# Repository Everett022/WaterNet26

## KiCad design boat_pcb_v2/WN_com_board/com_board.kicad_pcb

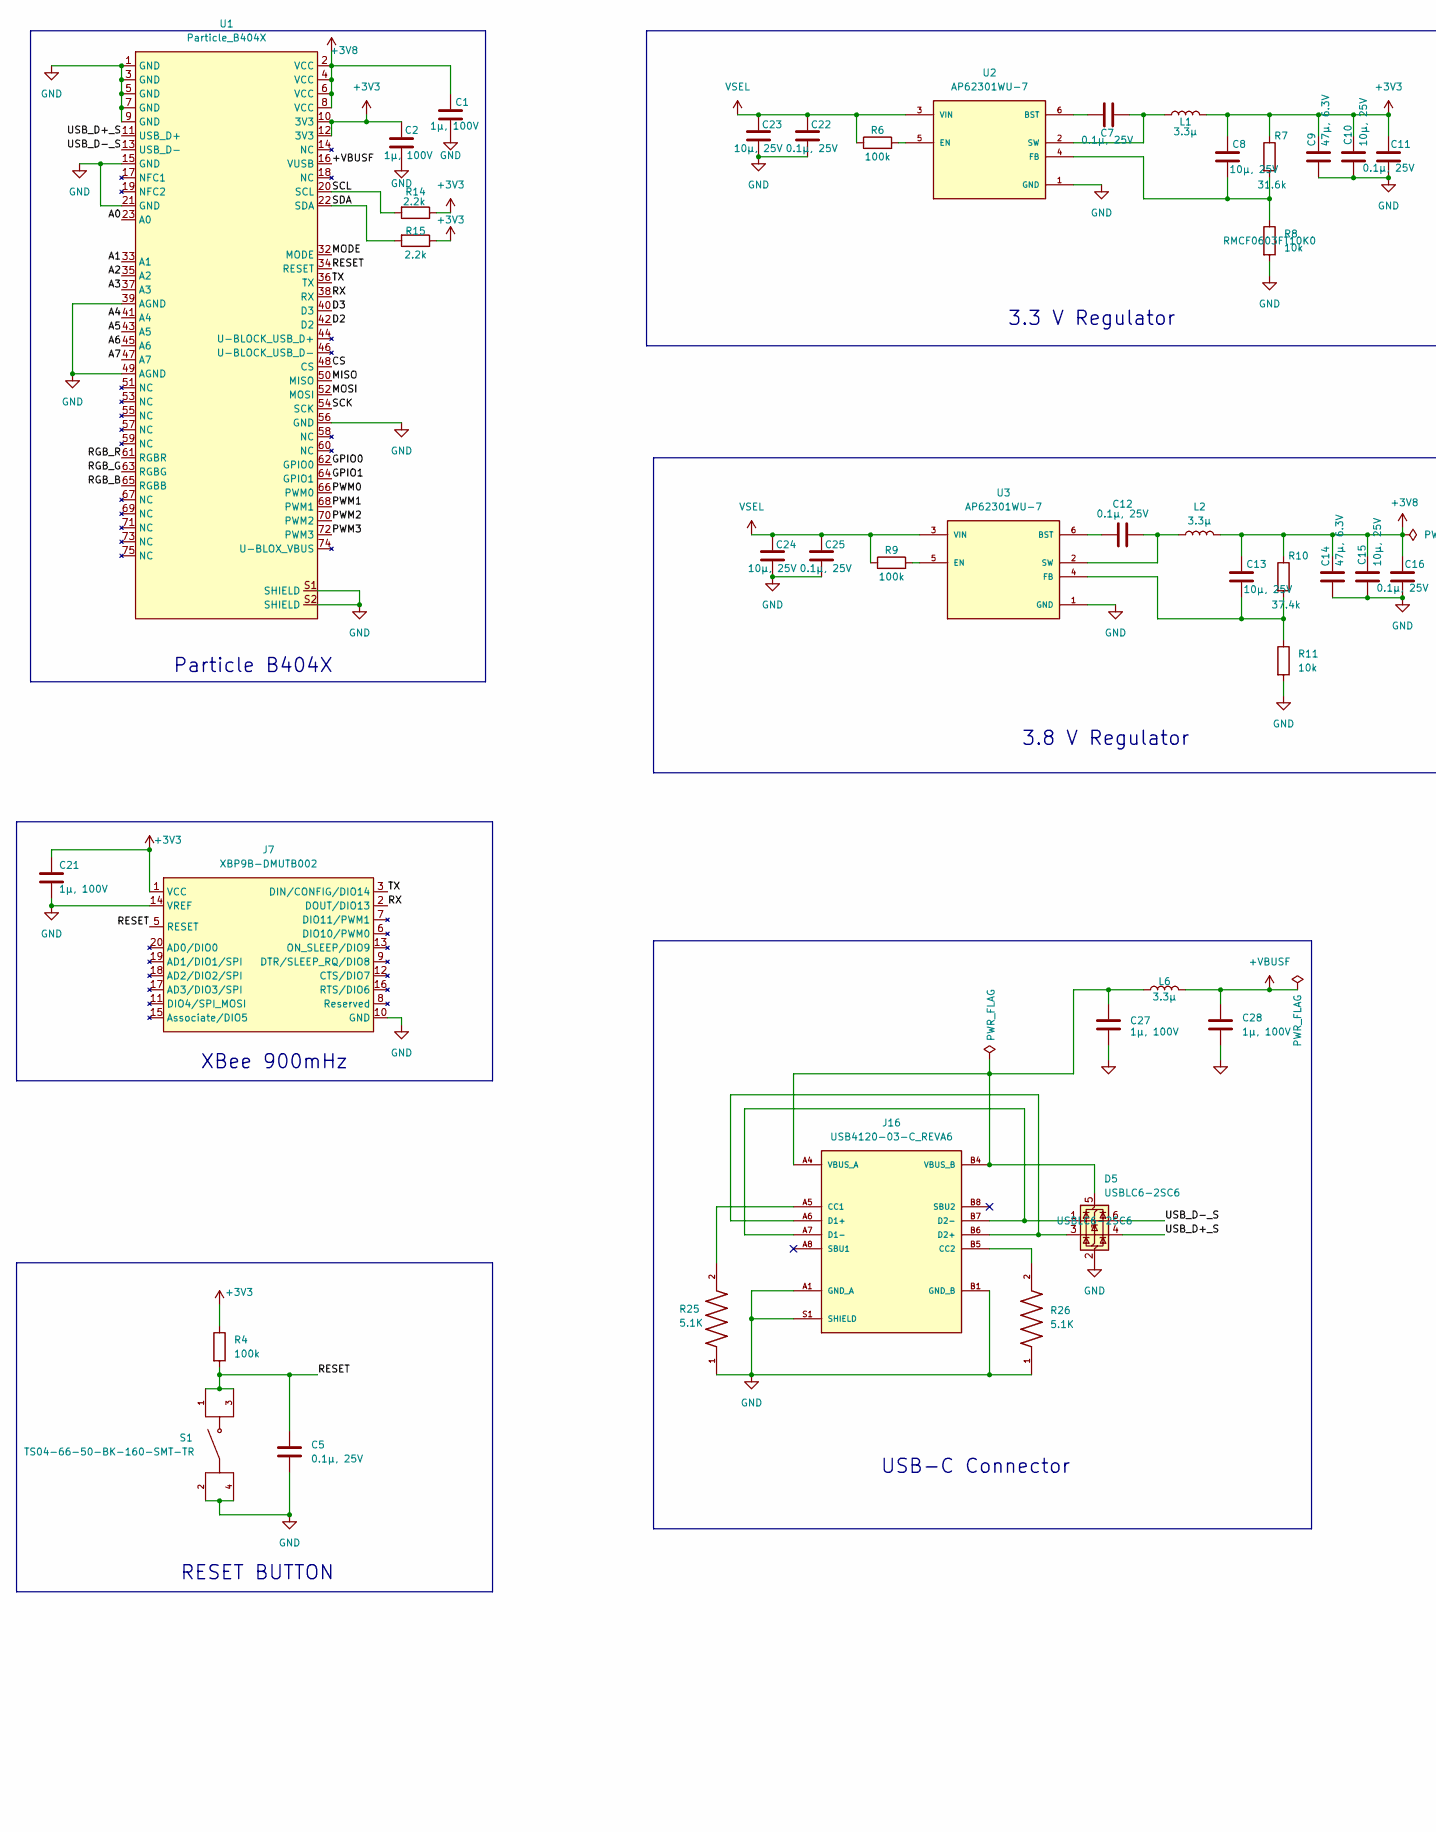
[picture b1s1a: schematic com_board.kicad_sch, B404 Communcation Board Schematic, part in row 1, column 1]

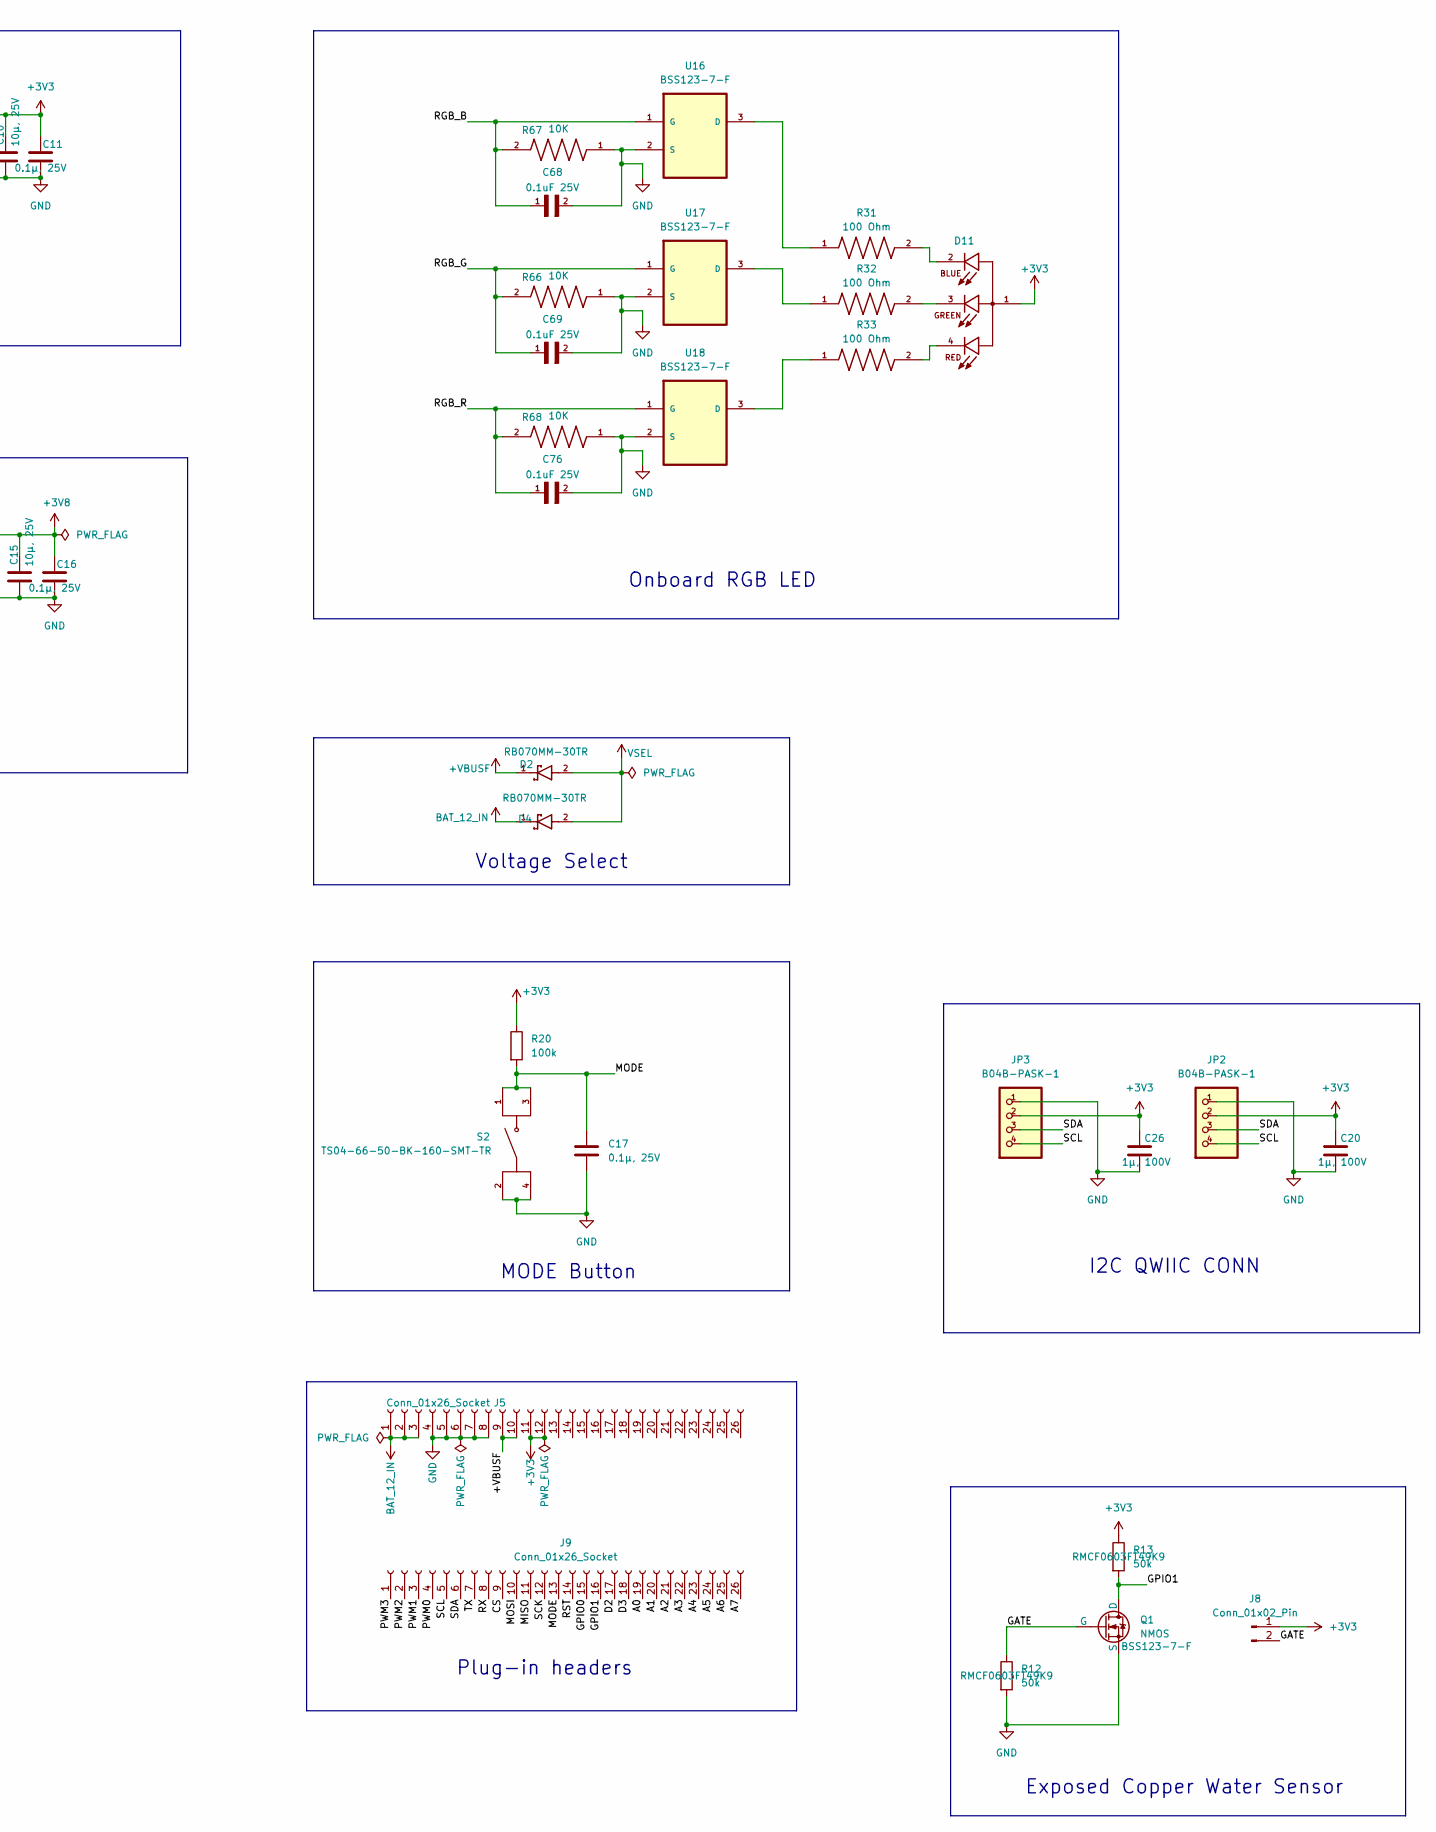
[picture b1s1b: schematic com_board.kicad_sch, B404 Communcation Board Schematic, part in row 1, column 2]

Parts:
C1, C2, C20, C21, C26, C27, C28: 1µ, 100V; CAPC2012X145N
C5, C7, C11, C12, C16, C17, C22, C25: 0.1µ, 25V; CAPC2012X95N
C8, C10, C13, C15, C23, C24: 10µ, 25V; CAPC2012X145N
C9, C14: 47µ, 6.3V; CAPC3216X180N
C68, C69, C76: 0.1uF 25V; CAPC2012X95N
D2, D4: RB070MM-30TR; DIO_RB070MM-30TR
D5: USBLC6-2SC6; SOT-23-6
D11: CLMVC-FKA-CL1D1L71BB7C3C3; LED_CLMVC-FKA-CL1D1L71BB7C3C3; PARTREV 14
J5, J9: Conn_01x26_Socket; PinHeader_1x26_P2.54mm_Vertical
J7: XBP9B-DMUTB002; SULLINS_NPPN101BFCN-RC
J8: Conn_01x02_Pin; PinHeader_1x02_P2.54mm_Vertical
J16: USB4120-03-C_REVA6; GCT_USB4120-03-C_REVA6; PARTREV A6
JP2, JP3: B04B-PASK-1
L1, L2, L6: 3.3µ; INDC1608X95N
Q1: NMOS; SOT95P240X110-3N
R4, R6, R9, R20: 100k; RES_ERA6AEB104V
R7: 31.6k; RES_ERA6AEB3162V
R8, R11: 10k; RES_ERA6AEB103V
R10: 37.4k; RESC1608X55N
R12, R13: 50k; RESC1608X55N
R14, R15: 2.2k; RESC1608X55N
R25, R26: 5.1K; RESC1508X55N
R31, R32, R33: 100 Ohm; RES_ERJ3EKF1000V; PARTREV 3/1/2020
R66, R67, R68: 10K; RES_ERA6AEB103V; PARTREV 3/1/2020
S1, S2: TS04-66-50-BK-160-SMT-TR; SW_TS04-66-50-BK-160-SMT-TR; PARTREV 1.04mm
U1: Particle_B404X; b404x
U2, U3: AP62301WU-7; SOT95P280X100-6N; PARTREV Rev. 3 - 2
U16, U17, U18: BSS123-7-F; SOT95P240X110-3N; MPN BSS123-7-F

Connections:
+3V3: C2.1, C8.1, C9.1, C10.1, C11.1, C20.1, C21.1, C26.1, D11.1, J5.11, J5.12, J7.1 (VCC), J8.1, JP2.2, JP3.2, L1.2, R4.1, R7.1, R13.1, R14.1, R15.1, R20.1, U1.10 (3V3), U1.12 (3V3); also elsewhere on the board
+3V8: C1.1, C13.1, C14.1, C15.1, C16.1, L2.2, R10.1, U1.2 (VCC), U1.4 (VCC), U1.6 (VCC), U1.8 (VCC)
+VBUSF: C28.1, D2.1, J5.9, J5.10, L6.2, U1.16 (VUSB); also elsewhere on the board
/A0: J9.19, U1.23 (A0)
/A1: J9.20, U1.33 (A1)
/A2: J9.21, U1.35 (A2)
/A3: J9.22, U1.37 (A3)
/A4: J9.23, U1.41 (A4)
/A5: J9.24, U1.43 (A5)
/A6: J9.25, U1.45 (A6)
/A7: J9.26, U1.47 (A7)
/CS: J9.9, U1.48 (CS)
/D2: J9.17, U1.42 (D2)
/D3: J9.18, U1.40 (D3)
/GATE: J8.2, Q1.2 (G), R12.1
/GPIO0: J9.15, U1.62 (GPIO0)
/GPIO1: J9.16, Q1.1 (D), R13.2, U1.64 (GPIO1)
/MISO: J9.11, U1.50 (MISO)
/MODE: C17.1, J9.13, R20.2, S2.1, S2.3, U1.32 (MODE)
/MOSI: J9.10, U1.52 (MOSI)
/PWM0: J9.4, U1.66 (PWM0)
/PWM1: J9.3, U1.68 (PWM1)
/PWM2: J9.2, U1.70 (PWM2)
/PWM3: J9.1, U1.72 (PWM3)
/RESET: C5.1, J7.5 (RESET), R4.2, S1.1, S1.3, U1.34 (RESET)
/RGB_B: C68.1, R67.2, U1.65 (RGBB), U16.1 (G)
/RGB_G: C69.1, R66.2, U1.63 (RGBG), U17.1 (G)
/RGB_R: C76.1, R68.2, U1.61 (RGBR), U18.1 (G)
/RST: J9.14
/RX: J7.2 (DOUT/DIO13), J9.8, U1.38 (RX)
/SCK: J9.12, U1.54 (SCK)
/SCL: J9.5, JP2.4, JP3.4, R14.2, U1.20 (SCL)
/SDA: J9.6, JP2.3, JP3.3, R15.2, U1.22 (SDA)
/TX: J7.3 (DIN/CONFIG/DIO14), J9.7, U1.36 (TX)
/USB_D+_S: D5.4 (I/O2), U1.11 (USB_D+); also elsewhere on the board
/USB_D-_S: D5.6 (I/O1), U1.13 (USB_D-); also elsewhere on the board
BAT_12_IN: D4.1, J5.1, J5.2, J5.3
GND: C1.2, C2.2, C5.2, C9.2, C10.2, C11.2, C14.2, C15.2, C16.2, C17.2, C20.2, C21.2, C22.2, C23.2, C24.2, C25.2, C26.2, C27.2, C28.2, C68.2, C69.2, C76.2, D5.2 (GND), J5.4, J5.5, J5.6, J5.7, J5.8, J7.10 (GND), J7.14 (VREF), J16.A1 (GND_A), J16.A12 (GND_A), J16.B1 (GND_B), J16.B12 (GND_B), J16.S1 (SHIELD), J16.S2 (SHIELD), J16.S3 (SHIELD), J16.S4 (SHIELD), JP2.1, JP3.1, Q1.3 (S), R8.2, R11.2, R12.2, R25.1, R26.1, R66.1, R67.1, R68.1, S1.2, S1.4, S2.2, S2.4, U1.1 (GND), U1.3 (GND), U1.5 (GND), U1.7 (GND), U1.9 (GND), U1.15 (GND), U1.21 (GND), U1.39 (AGND), U1.49 (AGND), U1.56 (GND), U1.S1 (SHIELD), U1.S2 (SHIELD), U2.1 (GND), U3.1 (GND), U16.2 (S), U17.2 (S), U18.2 (S); also elsewhere on the board
unnamed: D11.2, R31.2
unnamed: D11.3, R32.2
unnamed: D11.4, R33.2
unnamed: J16.A5 (CC1), R25.2
unnamed: J16.B5 (CC2), R26.2
unnamed: D5.3 (I/O2), J16.A6 (D1+), J16.B6 (D2+)
unnamed: D5.1 (I/O1), J16.A7 (D1-), J16.B7 (D2-)
unnamed: C7.1, U2.6 (BST)
unnamed: R6.2, U2.5 (EN)
unnamed: C8.2, R7.2, R8.1, U2.4 (FB)
unnamed: C7.2, L1.1, U2.2 (SW)
unnamed: C12.1, U3.6 (BST)
unnamed: R9.2, U3.5 (EN)
unnamed: C13.2, R10.2, R11.1, U3.4 (FB)
unnamed: C12.2, L2.1, U3.2 (SW)
unnamed: R31.1, U16.3 (D)
unnamed: R32.1, U17.3 (D)
unnamed: R33.1, U18.3 (D)
VBUS_A: C27.1, D5.5 (VBUS), J16.A4 (VBUS_A), J16.A9 (VBUS_A), J16.B4 (VBUS_B), J16.B9 (VBUS_B), L6.1
VSEL: C22.1, C23.1, C24.1, C25.1, D2.2, D4.2, R6.1, R9.1, U2.3 (VIN), U3.3 (VIN)

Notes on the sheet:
Voltage Select
Particle B404X
Plug-in headers
XBee 900mHz
Exposed Copper Water Sensor
RESET BUTTON
3.3 V Regulator
3.8 V Regulator
Onboard RGB LED
MODE Button
USB-C Connector
I2C QWIIC CONN

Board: 2 copper layers, 81 parts (0 on the bottom side), 67 nets, no tracks yet.

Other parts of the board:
C3, C4: 1µ, 25V; C_0603_1608Metric_Pad1.08x0.95mm_HandSolder
D1: USBLC6-2SC6; SOT-23-6
D3: CLMVC-FKA-CL1D1L71BB7C3C3; LED_CLMVC-FKA-CL1D1L71BB7C3C3
J2: USB_C_Receptacle_USB2.0_16P; USB_C_Plug_ShenzhenJingTuoJin_918-118A2021Y40002_Vertical
L3: 3.3µ; INDC1608X95N
R2, R3: 5.1k; R_0603_1608Metric
R16: 0R; R_0603_1608Metric
R17, R18, R19: 330; R_0603_1608Metric

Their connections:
+3V3: R16.1; also elsewhere on the board
+VBUS: C3.1, D1.5 (VBUS), J2.A4 (VBUS), J2.A9 (VBUS), J2.B4 (VBUS), J2.B9 (VBUS), L3.1
+VBUSF: C4.1, L3.2; also elsewhere on the board
/RGBR: R17.2, R19.2
/USBCC1: J2.A5 (CC1), R3.1
/USBCC2: J2.B5 (CC2), R2.1
/USB_D+: D1.3 (I/O2), J2.A6 (D+), J2.B6 (D+)
/USB_D+_S: D1.4 (I/O2); also elsewhere on the board
/USB_D-: D1.1 (I/O1), J2.A7 (D-), J2.B7 (D-)
/USB_D-_S: D1.6 (I/O1); also elsewhere on the board
GND: C3.2, C4.2, D1.2 (GND), J2.A1 (GND), J2.A12 (GND), J2.B1 (GND), J2.B12 (GND), J2.S1 (SHIELD), R2.2, R3.2; also elsewhere on the board
unnamed: D3.1, R16.2
unnamed: D3.2, R19.1
unnamed: D3.3, R18.1
unnamed: D3.4, R17.1

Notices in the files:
parts and their libraries:
COPYRIGHT: Copyright (C) 2024 Ultra Librarian. All rights reserved.
COPYRIGHT: Copyright (C) 2023 Ultra Librarian. All rights reserved.
